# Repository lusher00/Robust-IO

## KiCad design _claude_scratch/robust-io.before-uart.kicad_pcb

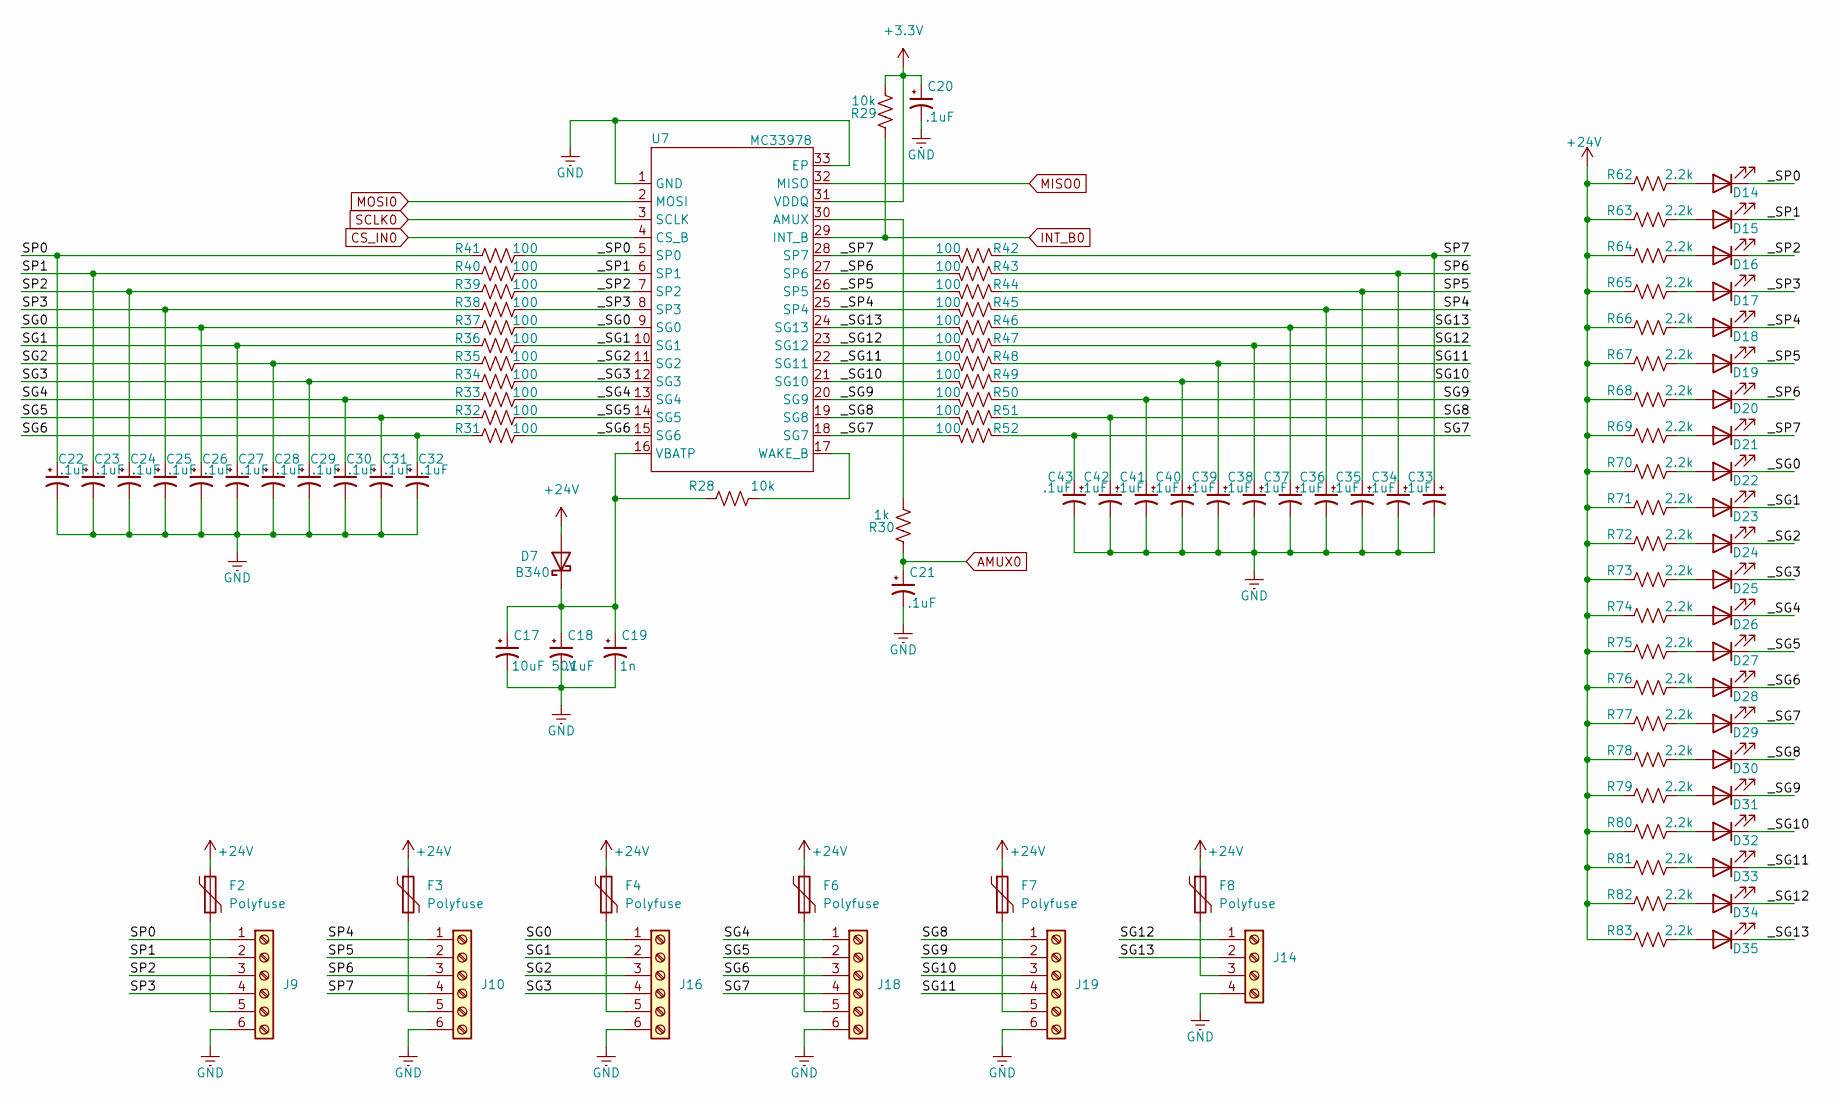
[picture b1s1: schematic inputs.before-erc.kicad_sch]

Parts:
C17: 10uF 50V; C_0805_2012Metric
C18, C20, C21, C22, C23, C24, C25, C26, C27, C28, C29, C30, C31, C32, C33, C34, C35, C36, C37, C38, C39, C40, C41, C42, C43: .1uF; C_0603_1608Metric
C19: 1n; C_0603_1608Metric
D7: B340; D_SMC
D14, D15, D16, D17, D18, D19, D20, D21, D22, D23, D24, D25, D26, D27, D28, D29, D30, D31, D32, D33, D34, D35: LED; LED_0603_1608Metric
F2, F3, F4, F6, F7, F8: Polyfuse; Fuse_1206_3216Metric
J9, J10, J16, J18, J19: Screw_Terminal_01x06; PhoenixContact_MC_1,5_6-G-3.5_1x06_P3.50mm_Horizontal
J14: Screw_Terminal_01x04; PhoenixContact_MC_1,5_4-G-3.5_1x04_P3.50mm_Horizontal
R28, R29: 10k; R_0603_1608Metric_Pad0.98x0.95mm_HandSolder
R30: 1k; R_0603_1608Metric_Pad0.98x0.95mm_HandSolder
R31, R32, R33, R34, R35, R36, R37, R38, R39, R40, R41, R42, R43, R44, R45, R46, R47, R48, R49, R50, R51, R52: 100; R_0603_1608Metric_Pad0.98x0.95mm_HandSolder
R62, R63, R64, R65, R66, R67, R68, R69, R70, R71, R72, R73, R74, R75, R76, R77, R78, R79, R80, R81, R82, R83: 2.2k; R_1206_3216Metric
U7: MC33978; HSOP-32-1EP_7.5x11mm_P0.65mm_EP4.7x4.7mm; Manufacturer Part MC33978AEKR2; LCSC Part Name MC33978AEKR2

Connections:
+3.3V: C20.1, R29.2, U7.31 (VDDQ); also elsewhere on the board
+24V: D7.2 (A), F2.1, F3.1, F4.1, F6.1, F7.1, F8.1, R62.1, R63.1, R64.1, R65.1, R66.1, R67.1, R68.1, R69.1, R70.1, R71.1, R72.1, R73.1, R74.1, R75.1, R76.1, R77.1, R78.1, R79.1, R80.1, R81.1, R82.1, R83.1; also elsewhere on the board
/inputs/SG0: C26.1, J16.1, R37.1
/inputs/SG1: C27.1, J16.2, R36.1
/inputs/SG2: C28.1, J16.3, R35.1
/inputs/SG3: C29.1, J16.4, R34.1
/inputs/SG4: C30.1, J18.1, R33.1
/inputs/SG5: C31.1, J18.2, R32.1
/inputs/SG6: C32.1, J18.3, R31.1
/inputs/SG7: C43.1, J18.4, R52.1
/inputs/SG8: C42.1, J19.1, R51.1
/inputs/SG9: C41.1, J19.2, R50.1
/inputs/SG10: C40.1, J19.3, R49.1
/inputs/SG11: C39.1, J19.4, R48.1
/inputs/SG12: C38.1, J14.1, R47.1
/inputs/SG13: C37.1, J14.2, R46.1
/inputs/SP0: C22.1, J9.1, R41.1
/inputs/SP1: C23.1, J9.2, R40.1
/inputs/SP2: C24.1, J9.3, R39.1
/inputs/SP3: C25.1, J9.4, R38.1
/inputs/SP4: C36.1, J10.1, R45.1
/inputs/SP5: C35.1, J10.2, R44.1
/inputs/SP6: C34.1, J10.3, R43.1
/inputs/SP7: C33.1, J10.4, R42.1
/inputs/_SG0: D22.1 (K), R37.2, U7.9 (SG0)
/inputs/_SG1: D23.1 (K), R36.2, U7.10 (SG1)
/inputs/_SG2: D24.1 (K), R35.2, U7.11 (SG2)
/inputs/_SG3: D25.1 (K), R34.2, U7.12 (SG3)
/inputs/_SG4: D26.1 (K), R33.2, U7.13 (SG4)
/inputs/_SG5: D27.1 (K), R32.2, U7.14 (SG5)
/inputs/_SG6: D28.1 (K), R31.2, U7.15 (SG6)
/inputs/_SG7: D29.1 (K), R52.2, U7.18 (SG7)
/inputs/_SG8: D30.1 (K), R51.2, U7.19 (SG8)
/inputs/_SG9: D31.1 (K), R50.2, U7.20 (SG9)
/inputs/_SG10: D32.1 (K), R49.2, U7.21 (SG10)
/inputs/_SG11: D33.1 (K), R48.2, U7.22 (SG11)
/inputs/_SG12: D34.1 (K), R47.2, U7.23 (SG12)
/inputs/_SG13: D35.1 (K), R46.2, U7.24 (SG13)
/inputs/_SP0: D14.1 (K), R41.2, U7.5 (SP0)
/inputs/_SP1: D15.1 (K), R40.2, U7.6 (SP1)
/inputs/_SP2: D16.1 (K), R39.2, U7.7 (SP2)
/inputs/_SP3: D17.1 (K), R38.2, U7.8 (SP3)
/inputs/_SP4: D18.1 (K), R45.2, U7.25 (SP4)
/inputs/_SP5: D19.1 (K), R44.2, U7.26 (SP5)
/inputs/_SP6: D20.1 (K), R43.2, U7.27 (SP6)
/inputs/_SP7: D21.1 (K), R42.2, U7.28 (SP7)
AMUX0: C21.1, R30.1; also elsewhere on the board
CS_IN0: U7.4 (CS_B); also elsewhere on the board
GND: C17.2, C18.2, C19.2, C20.2, C21.2, C22.2, C23.2, C24.2, C25.2, C26.2, C27.2, C28.2, C29.2, C30.2, C31.2, C32.2, C33.2, C34.2, C35.2, C36.2, C37.2, C38.2, C39.2, C40.2, C41.2, C42.2, C43.2, J9.6, J10.6, J14.4, J16.6, J18.6, J19.6, U7.1 (GND), U7.33 (EP); also elsewhere on the board
INT_B0: R29.1, U7.29 (INT_B); also elsewhere on the board
MISO0: U7.32 (MISO); also elsewhere on the board
MOSI0: U7.2 (MOSI); also elsewhere on the board
unnamed: C17.1, C18.1, C19.1, D7.1 (K), R28.1, U7.16 (VBATP)
unnamed: D14.2 (A), R62.2
unnamed: D15.2 (A), R63.2
unnamed: D16.2 (A), R64.2
unnamed: D17.2 (A), R65.2
unnamed: D18.2 (A), R66.2
unnamed: D19.2 (A), R67.2
unnamed: D20.2 (A), R68.2
unnamed: D21.2 (A), R69.2
unnamed: D22.2 (A), R70.2
unnamed: D23.2 (A), R71.2
unnamed: D24.2 (A), R72.2
unnamed: D25.2 (A), R73.2
unnamed: D26.2 (A), R74.2
unnamed: D27.2 (A), R75.2
unnamed: D28.2 (A), R76.2
unnamed: D29.2 (A), R77.2
unnamed: D30.2 (A), R78.2
unnamed: D31.2 (A), R79.2
unnamed: D32.2 (A), R80.2
unnamed: D33.2 (A), R81.2
unnamed: D34.2 (A), R82.2
unnamed: D35.2 (A), R83.2
unnamed: F2.2, J9.5
unnamed: F3.2, J10.5
unnamed: F8.2, J14.3
unnamed: F4.2, J16.5
unnamed: F6.2, J18.5
unnamed: F7.2, J19.5
unnamed: R30.2, U7.30 (AMUX)
unnamed: R28.2, U7.17 (WAKE_B)
SCLK0: U7.3 (SCLK); also elsewhere on the board

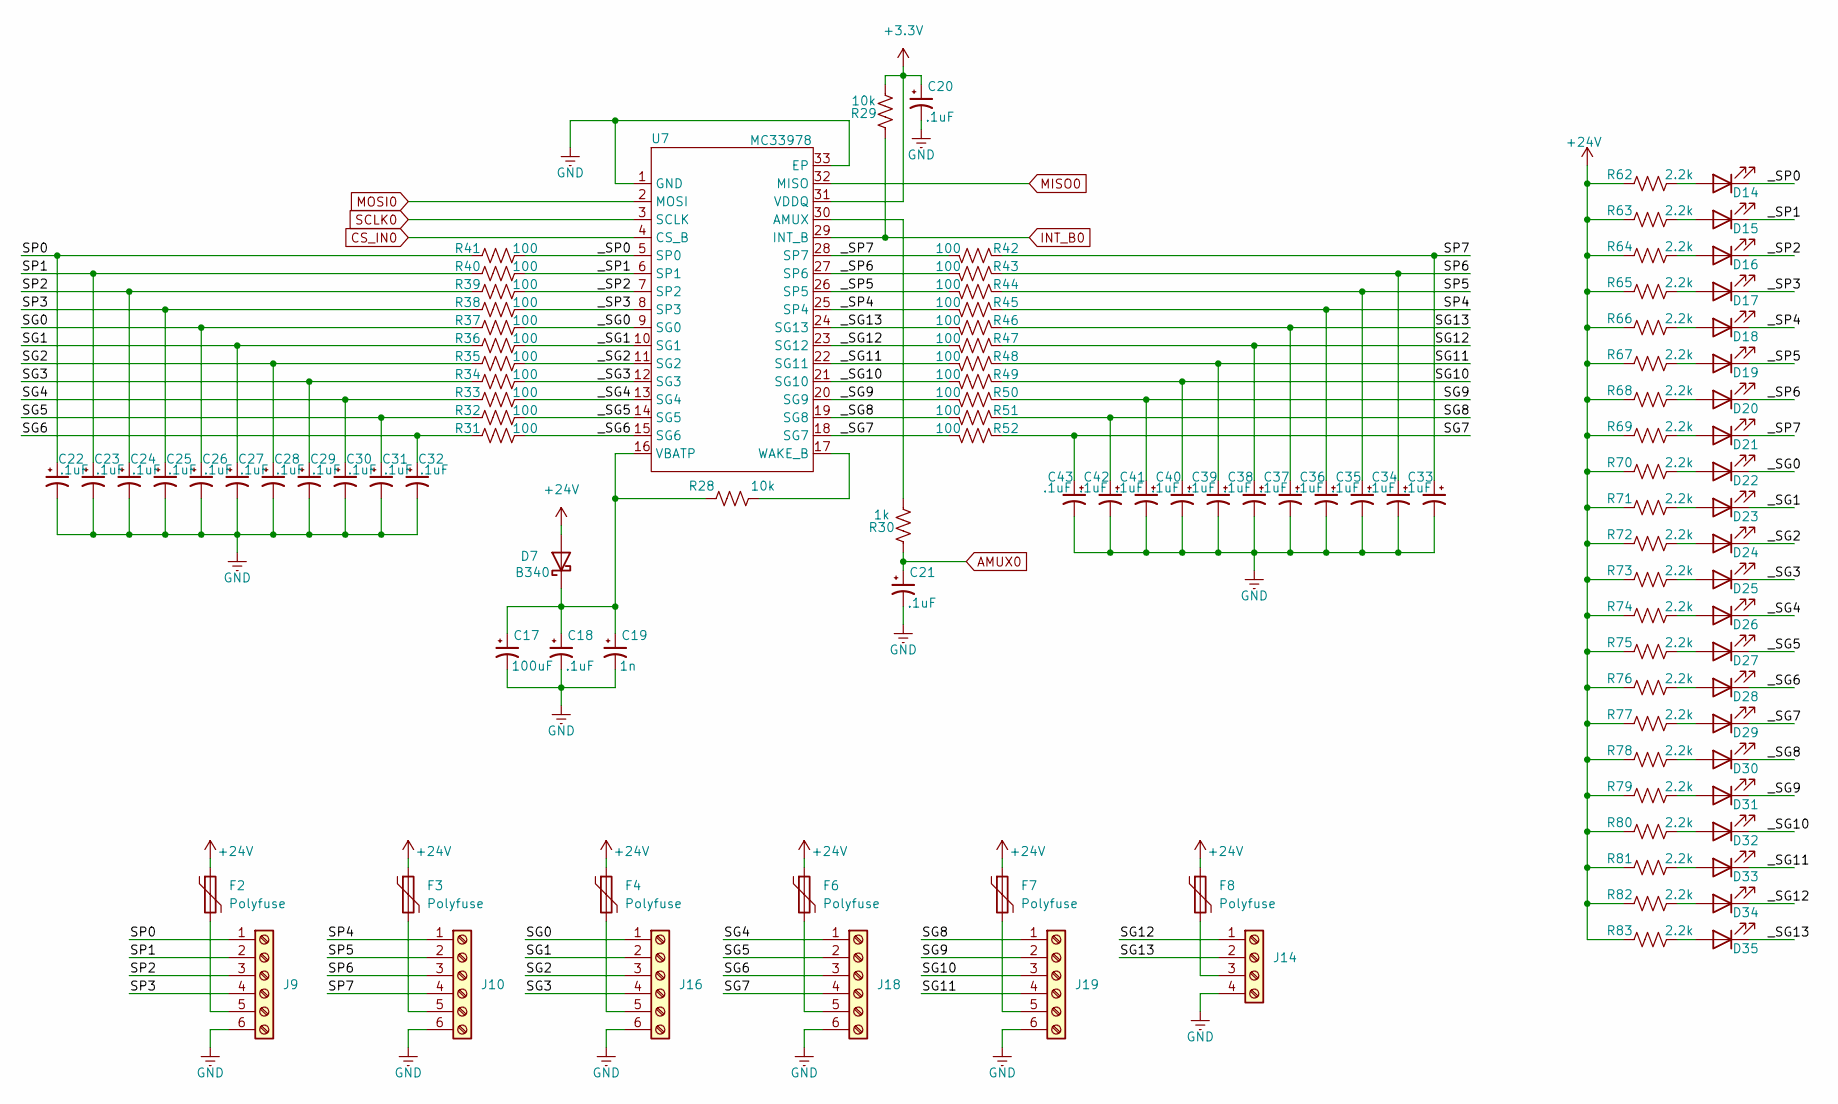
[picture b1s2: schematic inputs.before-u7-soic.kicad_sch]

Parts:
C17: 100uF; C_0603_1608Metric
C18, C20, C21, C22, C23, C24, C25, C26, C27, C28, C29, C30, C31, C32, C33, C34, C35, C36, C37, C38, C39, C40, C41, C42, C43: .1uF; C_0603_1608Metric
C19: 1n; C_0603_1608Metric
D7: B340; D_SMC
D14, D15, D16, D17, D18, D19, D20, D21, D22, D23, D24, D25, D26, D27, D28, D29, D30, D31, D32, D33, D34, D35: LED; LED_0603_1608Metric
F2, F3, F4, F6, F7, F8: Polyfuse; Fuse_1206_3216Metric
J9, J10, J16, J18, J19: Screw_Terminal_01x06; PhoenixContact_MC_1,5_6-G-3.5_1x06_P3.50mm_Horizontal
J14: Screw_Terminal_01x04; PhoenixContact_MC_1,5_4-G-3.5_1x04_P3.50mm_Horizontal
R28, R29: 10k; R_0603_1608Metric_Pad0.98x0.95mm_HandSolder
R30: 1k; R_0603_1608Metric_Pad0.98x0.95mm_HandSolder
R31, R32, R33, R34, R35, R36, R37, R38, R39, R40, R41, R42, R43, R44, R45, R46, R47, R48, R49, R50, R51, R52: 100; R_0603_1608Metric_Pad0.98x0.95mm_HandSolder
R62, R63, R64, R65, R66, R67, R68, R69, R70, R71, R72, R73, R74, R75, R76, R77, R78, R79, R80, R81, R82, R83: 2.2k; R_1206_3216Metric
U7: MC33978; QFN-32-1EP_5x5mm_P0.5mm_EP3.7x3.7mm_ThermalVias; Manufacturer Part MC33978AEKR2; LCSC Part Name MC33978AEKR2

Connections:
+3.3V: C20.1, R29.2, U7.31 (VDDQ); also elsewhere on the board
+24V: D7.2 (A), F2.1, F3.1, F4.1, F6.1, F7.1, F8.1, R62.1, R63.1, R64.1, R65.1, R66.1, R67.1, R68.1, R69.1, R70.1, R71.1, R72.1, R73.1, R74.1, R75.1, R76.1, R77.1, R78.1, R79.1, R80.1, R81.1, R82.1, R83.1; also elsewhere on the board
/inputs/SG0: C26.1, J16.1, R37.1
/inputs/SG1: C27.1, J16.2, R36.1
/inputs/SG2: C28.1, J16.3, R35.1
/inputs/SG3: C29.1, J16.4, R34.1
/inputs/SG4: C30.1, J18.1, R33.1
/inputs/SG5: C31.1, J18.2, R32.1
/inputs/SG6: C32.1, J18.3, R31.1
/inputs/SG7: C43.1, J18.4, R52.1
/inputs/SG8: C42.1, J19.1, R51.1
/inputs/SG9: C41.1, J19.2, R50.1
/inputs/SG10: C40.1, J19.3, R49.1
/inputs/SG11: C39.1, J19.4, R48.1
/inputs/SG12: C38.1, J14.1, R47.1
/inputs/SG13: C37.1, J14.2, R46.1
/inputs/SP0: C22.1, J9.1, R41.1
/inputs/SP1: C23.1, J9.2, R40.1
/inputs/SP2: C24.1, J9.3, R39.1
/inputs/SP3: C25.1, J9.4, R38.1
/inputs/SP4: C36.1, J10.1, R45.1
/inputs/SP5: C35.1, J10.2, R44.1
/inputs/SP6: C34.1, J10.3, R43.1
/inputs/SP7: C33.1, J10.4, R42.1
/inputs/_SG0: D22.1 (K), R37.2, U7.9 (SG0)
/inputs/_SG1: D23.1 (K), R36.2, U7.10 (SG1)
/inputs/_SG2: D24.1 (K), R35.2, U7.11 (SG2)
/inputs/_SG3: D25.1 (K), R34.2, U7.12 (SG3)
/inputs/_SG4: D26.1 (K), R33.2, U7.13 (SG4)
/inputs/_SG5: D27.1 (K), R32.2, U7.14 (SG5)
/inputs/_SG6: D28.1 (K), R31.2, U7.15 (SG6)
/inputs/_SG7: D29.1 (K), R52.2, U7.18 (SG7)
/inputs/_SG8: D30.1 (K), R51.2, U7.19 (SG8)
/inputs/_SG9: D31.1 (K), R50.2, U7.20 (SG9)
/inputs/_SG10: D32.1 (K), R49.2, U7.21 (SG10)
/inputs/_SG11: D33.1 (K), R48.2, U7.22 (SG11)
/inputs/_SG12: D34.1 (K), R47.2, U7.23 (SG12)
/inputs/_SG13: D35.1 (K), R46.2, U7.24 (SG13)
/inputs/_SP0: D14.1 (K), R41.2, U7.5 (SP0)
/inputs/_SP1: D15.1 (K), R40.2, U7.6 (SP1)
/inputs/_SP2: D16.1 (K), R39.2, U7.7 (SP2)
/inputs/_SP3: D17.1 (K), R38.2, U7.8 (SP3)
/inputs/_SP4: D18.1 (K), R45.2, U7.25 (SP4)
/inputs/_SP5: D19.1 (K), R44.2, U7.26 (SP5)
/inputs/_SP6: D20.1 (K), R43.2, U7.27 (SP6)
/inputs/_SP7: D21.1 (K), R42.2, U7.28 (SP7)
AMUX0: C21.1, R30.1; also elsewhere on the board
CS_IN0: U7.4 (CS_B); also elsewhere on the board
GND: C17.2, C18.2, C19.2, C20.2, C21.2, C22.2, C23.2, C24.2, C25.2, C26.2, C27.2, C28.2, C29.2, C30.2, C31.2, C32.2, C33.2, C34.2, C35.2, C36.2, C37.2, C38.2, C39.2, C40.2, C41.2, C42.2, C43.2, J9.6, J10.6, J14.4, J16.6, J18.6, J19.6, U7.1 (GND), U7.33 (EP); also elsewhere on the board
INT_B0: R29.1, U7.29 (INT_B); also elsewhere on the board
MISO0: U7.32 (MISO); also elsewhere on the board
MOSI0: U7.2 (MOSI); also elsewhere on the board
unnamed: C17.1, C18.1, C19.1, D7.1 (K), R28.1, U7.16 (VBATP)
unnamed: D14.2 (A), R62.2
unnamed: D15.2 (A), R63.2
unnamed: D16.2 (A), R64.2
unnamed: D17.2 (A), R65.2
unnamed: D18.2 (A), R66.2
unnamed: D19.2 (A), R67.2
unnamed: D20.2 (A), R68.2
unnamed: D21.2 (A), R69.2
unnamed: D22.2 (A), R70.2
unnamed: D23.2 (A), R71.2
unnamed: D24.2 (A), R72.2
unnamed: D25.2 (A), R73.2
unnamed: D26.2 (A), R74.2
unnamed: D27.2 (A), R75.2
unnamed: D28.2 (A), R76.2
unnamed: D29.2 (A), R77.2
unnamed: D30.2 (A), R78.2
unnamed: D31.2 (A), R79.2
unnamed: D32.2 (A), R80.2
unnamed: D33.2 (A), R81.2
unnamed: D34.2 (A), R82.2
unnamed: D35.2 (A), R83.2
unnamed: F2.2, J9.5
unnamed: F3.2, J10.5
unnamed: F8.2, J14.3
unnamed: F4.2, J16.5
unnamed: F6.2, J18.5
unnamed: F7.2, J19.5
unnamed: R30.2, U7.30 (AMUX)
unnamed: R28.2, U7.17 (WAKE_B)
SCLK0: U7.3 (SCLK); also elsewhere on the board

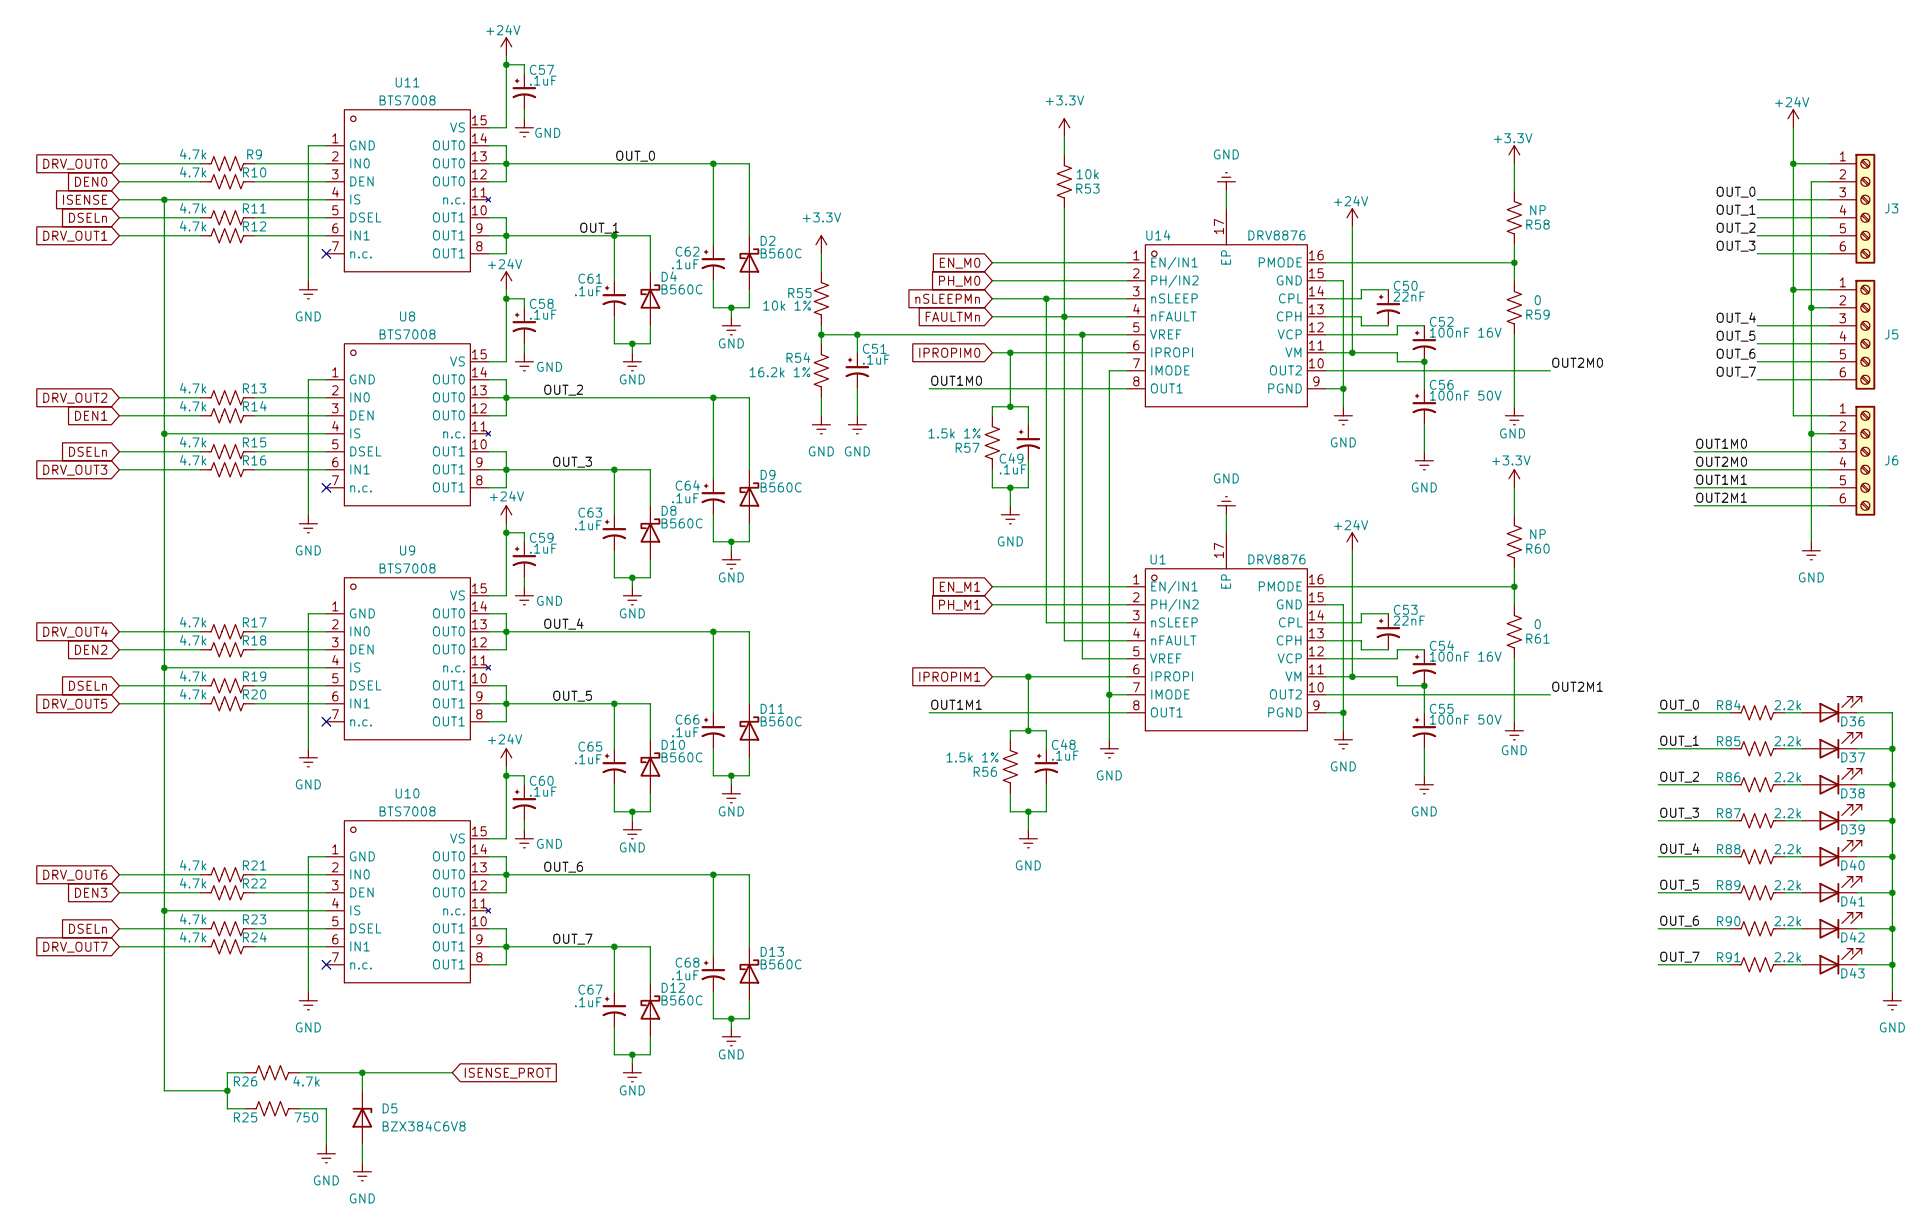
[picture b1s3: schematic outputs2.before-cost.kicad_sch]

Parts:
C48, C49, C51, C57, C58, C59, C60, C61, C62, C63, C64, C65, C66, C67, C68: .1uF; C_0603_1608Metric_Pad1.08x0.95mm_HandSolder
C50, C53: 22nF; C_0603_1608Metric_Pad1.08x0.95mm_HandSolder
C52, C54: 100nF 16V; C_0603_1608Metric_Pad1.08x0.95mm_HandSolder
C55, C56: 100nF 50V; C_0603_1608Metric_Pad1.08x0.95mm_HandSolder
D2, D4, D8, D9, D10, D11, D12, D13: B560C; D_SMC
D5: BZX384C6V8; D_SOD-323
D36, D37, D38, D39, D40, D41, D42, D43: LED; LED_0603_1608Metric
J3, J5, J6: Screw_Terminal_01x06; PhoenixContact_MSTBA_2,5_6-G-5,08_1x06_P5.08mm_Horizontal
R9, R10, R11, R12, R13, R14, R15, R16, R17, R18, R19, R20, R21, R22, R23, R24, R26: 4.7k; R_0603_1608Metric
R25: 750; R_0603_1608Metric
R53: 10k; R_0603_1608Metric_Pad0.98x0.95mm_HandSolder
R54: 16.2k 1%; R_0603_1608Metric_Pad0.98x0.95mm_HandSolder
R55: 10k 1%; R_0603_1608Metric_Pad0.98x0.95mm_HandSolder
R56, R57: 1.5k 1%; R_0603_1608Metric_Pad0.98x0.95mm_HandSolder
R58, R60: NP; R_0603_1608Metric_Pad0.98x0.95mm_HandSolder
R59, R61: 0; R_0603_1608Metric_Pad0.98x0.95mm_HandSolder
R84, R85, R86, R87, R88, R89, R90, R91: 2.2k; R_0603_1608Metric_Pad0.98x0.95mm_HandSolder
U1, U14: DRV8876; IC_DRV8876PWPR; Manufacturer Part DRV8876PWPR; LCSC Part Name 3.5A 有刷直流电机驱动芯片 5.5V
U8, U9, U10, U11: BTS7008; TSSOP-14-1EP_4.4x5mm_P0.65mm; Manufacturer Part BTS7008-2EPA; LCSC Part Name 12V智能高端功率开关

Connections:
+3.3V: R53.1, R55.1, R58.1, R60.1; also elsewhere on the board
+24V: C52.2, C54.2, C55.1, C56.1, C57.1, C58.1, C59.1, C60.1, J3.1, J5.1, J6.1, U1.11 (VM), U8.15 (VS), U9.15 (VS), U10.15 (VS), U11.15 (VS), U14.11 (VM); also elsewhere on the board
/outputs2/OUT1M0: J6.3, U14.8 (OUT1)
/outputs2/OUT1M1: J6.5, U1.8 (OUT1)
/outputs2/OUT2M0: J6.4, U14.10 (OUT2)
/outputs2/OUT2M1: J6.6, U1.10 (OUT2)
/outputs2/OUT_0: C62.1, D2.1 (K), J3.3, R84.1, U11.12 (OUT0), U11.13 (OUT0), U11.14 (OUT0)
/outputs2/OUT_1: C61.1, D4.1 (K), J3.4, R85.1, U11.8 (OUT1), U11.9 (OUT1), U11.10 (OUT1)
/outputs2/OUT_2: C64.1, D9.1 (K), J3.5, R86.1, U8.12 (OUT0), U8.13 (OUT0), U8.14 (OUT0)
/outputs2/OUT_3: C63.1, D8.1 (K), J3.6, R87.1, U8.8 (OUT1), U8.9 (OUT1), U8.10 (OUT1)
/outputs2/OUT_4: C66.1, D11.1 (K), J5.3, R88.1, U9.12 (OUT0), U9.13 (OUT0), U9.14 (OUT0)
/outputs2/OUT_5: C65.1, D10.1 (K), J5.4, R89.1, U9.8 (OUT1), U9.9 (OUT1), U9.10 (OUT1)
/outputs2/OUT_6: C68.1, D13.1 (K), J5.5, R90.1, U10.12 (OUT0), U10.13 (OUT0), U10.14 (OUT0)
/outputs2/OUT_7: C67.1, D12.1 (K), J5.6, R91.1, U10.8 (OUT1), U10.9 (OUT1), U10.10 (OUT1)
DEN0: R10.1; also elsewhere on the board
DEN1: R14.1; also elsewhere on the board
DEN2: R18.1; also elsewhere on the board
DEN3: R22.1; also elsewhere on the board
DRV_OUT0: R9.1; also elsewhere on the board
DRV_OUT1: R12.1; also elsewhere on the board
DRV_OUT2: R13.1; also elsewhere on the board
DRV_OUT3: R16.1; also elsewhere on the board
DRV_OUT4: R17.1; also elsewhere on the board
DRV_OUT5: R20.1; also elsewhere on the board
DRV_OUT6: R21.1; also elsewhere on the board
DRV_OUT7: R24.1; also elsewhere on the board
DSELn: R11.1, R15.1, R19.1, R23.1; also elsewhere on the board
EN_M0: U14.1 (EN/IN1); also elsewhere on the board
EN_M1: U1.1 (EN/IN1); also elsewhere on the board
FAULTMn: R53.2, U1.4 (nFAULT), U14.4 (nFAULT); also elsewhere on the board
GND: C48.2, C49.2, C51.2, C55.2, C56.2, C57.2, C58.2, C59.2, C60.2, C61.2, C62.2, C63.2, C64.2, C65.2, C66.2, C67.2, C68.2, D2.2 (A), D4.2 (A), D5.2 (A), D8.2 (A), D9.2 (A), D10.2 (A), D11.2 (A), D12.2 (A), D13.2 (A), D36.1 (K), D37.1 (K), D38.1 (K), D39.1 (K), D40.1 (K), D41.1 (K), D42.1 (K), D43.1 (K), J3.2, J5.2, J6.2, R25.1, R54.2, R56.2, R57.2, R59.2, R61.2, U1.7 (IMODE), U1.9 (PGND), U1.15 (GND), U1.17 (EP), U8.1 (GND), U9.1 (GND), U10.1 (GND), U11.1 (GND), U14.7 (IMODE), U14.9 (PGND), U14.15 (GND), U14.17 (EP); also elsewhere on the board
IPROPIM0: C49.1, R57.1, U14.6 (IPROPI); also elsewhere on the board
IPROPIM1: C48.1, R56.1, U1.6 (IPROPI); also elsewhere on the board
ISENSE: R25.2, R26.2, U8.4 (IS), U9.4 (IS), U10.4 (IS), U11.4 (IS)
ISENSE_PROT: D5.1 (K), R26.1; also elsewhere on the board
unnamed: D36.2 (A), R84.2
unnamed: D37.2 (A), R85.2
unnamed: D38.2 (A), R86.2
unnamed: D39.2 (A), R87.2
unnamed: D40.2 (A), R88.2
unnamed: D41.2 (A), R89.2
unnamed: D42.2 (A), R90.2
unnamed: D43.2 (A), R91.2
unnamed: C53.2, U1.13 (CPH)
unnamed: C53.1, U1.14 (CPL)
unnamed: R60.2, R61.1, U1.16 (PMODE)
unnamed: C54.1, U1.12 (VCP)
unnamed: C51.1, R54.1, R55.2, U1.5 (VREF), U14.5 (VREF)
unnamed: R14.2, U8.3 (DEN)
unnamed: R15.2, U8.5 (DSEL)
unnamed: R13.2, U8.2 (IN0)
unnamed: R16.2, U8.6 (IN1)
unnamed: R18.2, U9.3 (DEN)
unnamed: R19.2, U9.5 (DSEL)
unnamed: R17.2, U9.2 (IN0)
unnamed: R20.2, U9.6 (IN1)
unnamed: R22.2, U10.3 (DEN)
unnamed: R23.2, U10.5 (DSEL)
unnamed: R21.2, U10.2 (IN0)
unnamed: R24.2, U10.6 (IN1)
unnamed: R10.2, U11.3 (DEN)
unnamed: R11.2, U11.5 (DSEL)
unnamed: R9.2, U11.2 (IN0)
unnamed: R12.2, U11.6 (IN1)
unnamed: C50.2, U14.13 (CPH)
unnamed: C50.1, U14.14 (CPL)
unnamed: R58.2, R59.1, U14.16 (PMODE)
unnamed: C52.1, U14.12 (VCP)
PH_M0: U14.2 (PH/IN2); also elsewhere on the board
PH_M1: U1.2 (PH/IN2); also elsewhere on the board
nSLEEPMn: U1.3 (nSLEEP), U14.3 (nSLEEP); also elsewhere on the board

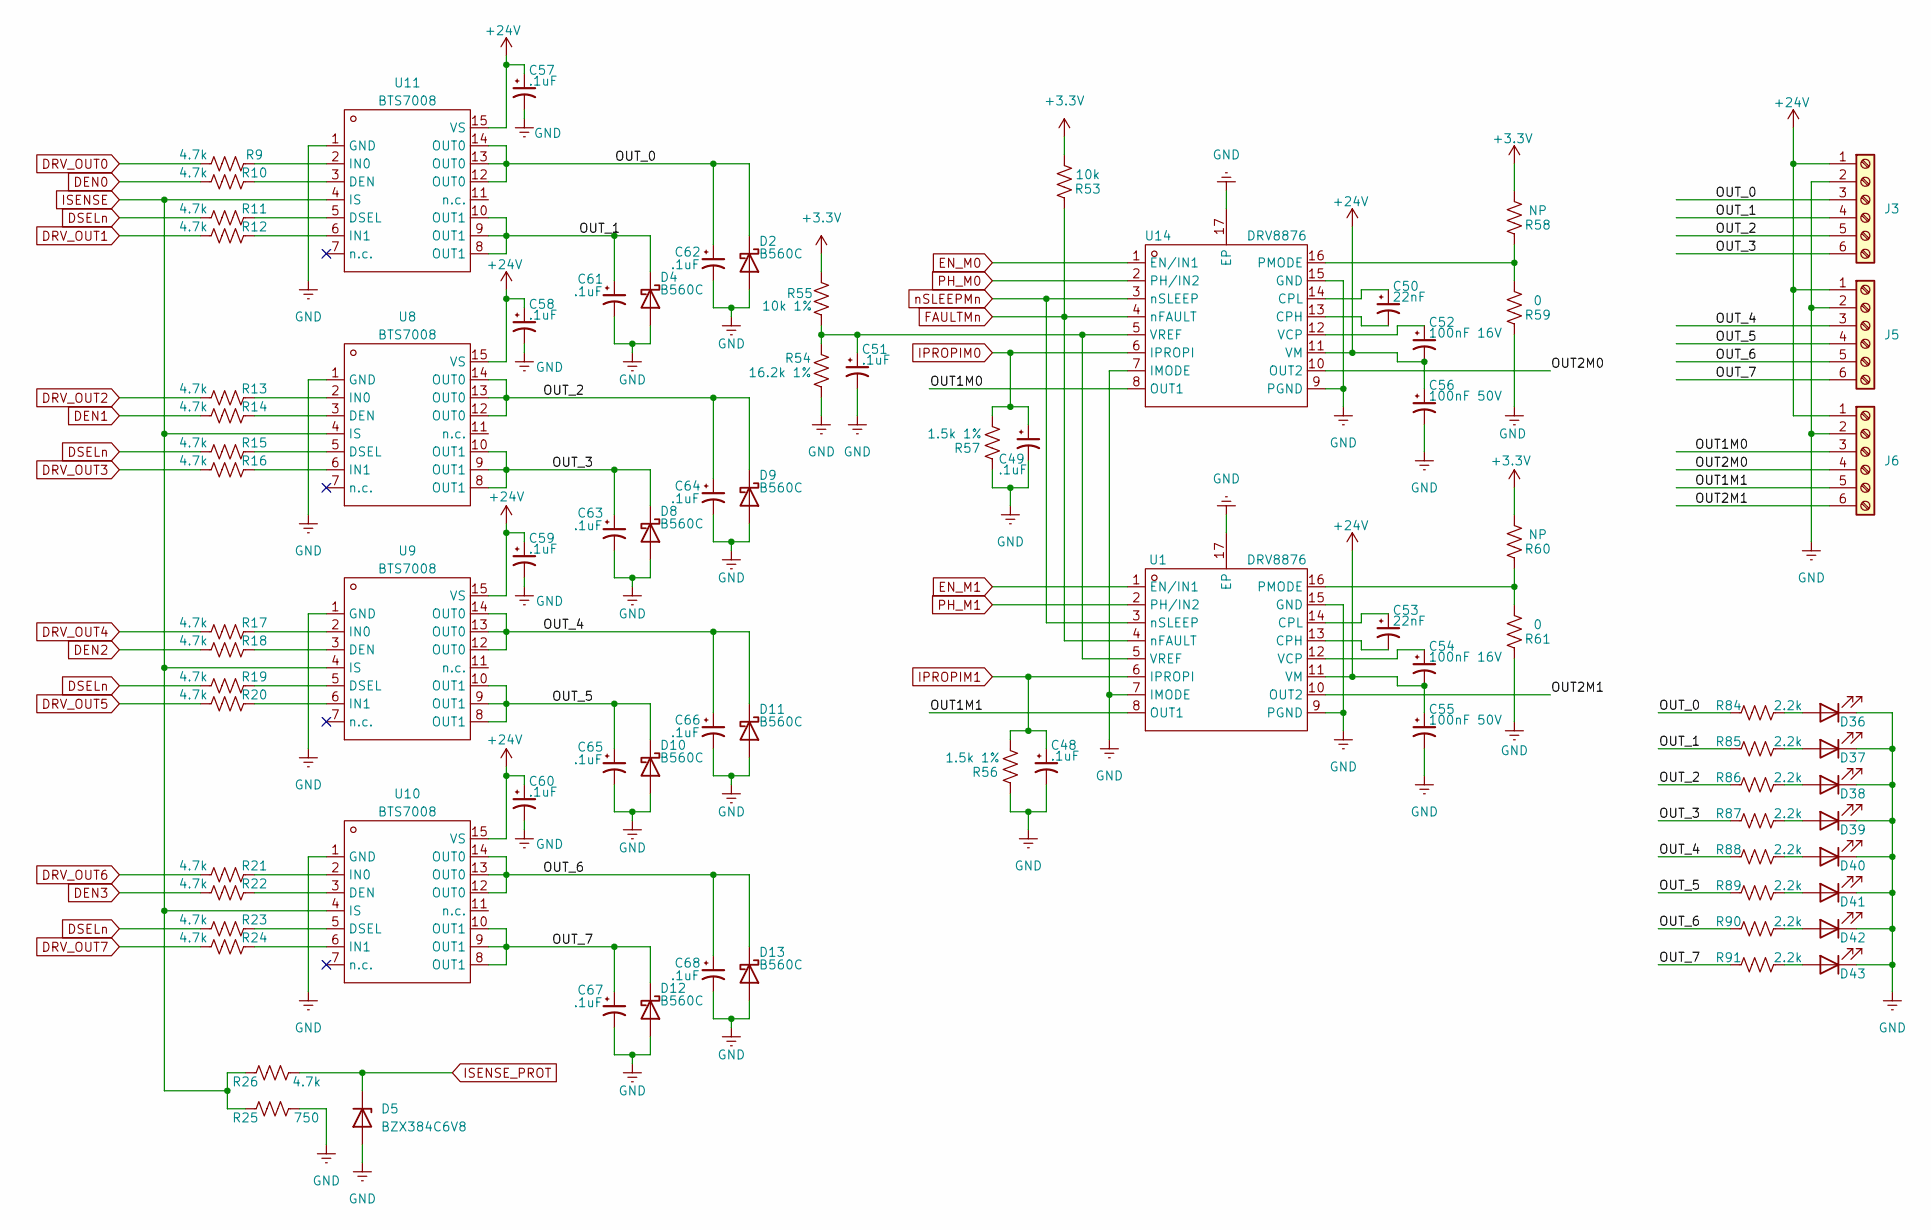
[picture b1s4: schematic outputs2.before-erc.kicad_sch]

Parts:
C48, C49, C51, C57, C58, C59, C60, C61, C62, C63, C64, C65, C66, C67, C68: .1uF; C_0603_1608Metric_Pad1.08x0.95mm_HandSolder
C50, C53: 22nF; C_0603_1608Metric_Pad1.08x0.95mm_HandSolder
C52, C54: 100nF 16V; C_0603_1608Metric_Pad1.08x0.95mm_HandSolder
C55, C56: 100nF 50V; C_0603_1608Metric_Pad1.08x0.95mm_HandSolder
D2, D4, D8, D9, D10, D11, D12, D13: B560C; D_SMC
D5: BZX384C6V8; D_SOD-323
D36, D37, D38, D39, D40, D41, D42, D43: LED; LED_0603_1608Metric
J3, J5, J6: Screw_Terminal_01x06; PhoenixContact_MSTBA_2,5_6-G-5,08_1x06_P5.08mm_Horizontal
R9, R10, R11, R12, R13, R14, R15, R16, R17, R18, R19, R20, R21, R22, R23, R24, R26: 4.7k; R_0603_1608Metric
R25: 750; R_0603_1608Metric
R53: 10k; R_0603_1608Metric_Pad0.98x0.95mm_HandSolder
R54: 16.2k 1%; R_0603_1608Metric_Pad0.98x0.95mm_HandSolder
R55: 10k 1%; R_0603_1608Metric_Pad0.98x0.95mm_HandSolder
R56, R57: 1.5k 1%; R_0603_1608Metric_Pad0.98x0.95mm_HandSolder
R58, R60: NP; R_0603_1608Metric_Pad0.98x0.95mm_HandSolder
R59, R61: 0; R_0603_1608Metric_Pad0.98x0.95mm_HandSolder
R84, R85, R86, R87, R88, R89, R90, R91: 2.2k; R_0603_1608Metric_Pad0.98x0.95mm_HandSolder
U1, U14: DRV8876; IC_DRV8876PWPR; Manufacturer Part DRV8876PWPR; LCSC Part Name 3.5A 有刷直流电机驱动芯片 5.5V
U8, U9, U10, U11: BTS7008; TSSOP-14-1EP_4.4x5mm_P0.65mm; Manufacturer Part BTS7008-2EPA; LCSC Part Name 12V智能高端功率开关

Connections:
+3.3V: R53.1, R55.1, R58.1, R60.1; also elsewhere on the board
+24V: C52.2, C54.2, C55.1, C56.1, C57.1, C58.1, C59.1, C60.1, J3.1, J5.1, J6.1, U1.11 (VM), U8.15 (VS), U9.15 (VS), U10.15 (VS), U11.15 (VS), U14.11 (VM); also elsewhere on the board
/outputs2/OUT1M0: J6.3, U14.8 (OUT1)
/outputs2/OUT1M1: J6.5, U1.8 (OUT1)
/outputs2/OUT2M0: J6.4, U14.10 (OUT2)
/outputs2/OUT2M1: J6.6, U1.10 (OUT2)
/outputs2/OUT_0: C62.1, D2.1 (K), J3.3, R84.1, U11.12 (OUT0), U11.13 (OUT0), U11.14 (OUT0)
/outputs2/OUT_1: C61.1, D4.1 (K), J3.4, R85.1, U11.8 (OUT1), U11.9 (OUT1), U11.10 (OUT1)
/outputs2/OUT_2: C64.1, D9.1 (K), J3.5, R86.1, U8.12 (OUT0), U8.13 (OUT0), U8.14 (OUT0)
/outputs2/OUT_3: C63.1, D8.1 (K), J3.6, R87.1, U8.8 (OUT1), U8.9 (OUT1), U8.10 (OUT1)
/outputs2/OUT_4: C66.1, D11.1 (K), J5.3, R88.1, U9.12 (OUT0), U9.13 (OUT0), U9.14 (OUT0)
/outputs2/OUT_5: C65.1, D10.1 (K), J5.4, R89.1, U9.8 (OUT1), U9.9 (OUT1), U9.10 (OUT1)
/outputs2/OUT_6: C68.1, D13.1 (K), J5.5, R90.1, U10.12 (OUT0), U10.13 (OUT0), U10.14 (OUT0)
/outputs2/OUT_7: C67.1, D12.1 (K), J5.6, R91.1, U10.8 (OUT1), U10.9 (OUT1), U10.10 (OUT1)
DEN0: R10.1; also elsewhere on the board
DEN1: R14.1; also elsewhere on the board
DEN2: R18.1; also elsewhere on the board
DEN3: R22.1; also elsewhere on the board
DRV_OUT0: R9.1; also elsewhere on the board
DRV_OUT1: R12.1; also elsewhere on the board
DRV_OUT2: R13.1; also elsewhere on the board
DRV_OUT3: R16.1; also elsewhere on the board
DRV_OUT4: R17.1; also elsewhere on the board
DRV_OUT5: R20.1; also elsewhere on the board
DRV_OUT6: R21.1; also elsewhere on the board
DRV_OUT7: R24.1; also elsewhere on the board
DSELn: R11.1, R15.1, R19.1, R23.1; also elsewhere on the board
EN_M0: U14.1 (EN/IN1); also elsewhere on the board
EN_M1: U1.1 (EN/IN1); also elsewhere on the board
FAULTMn: R53.2, U1.4 (nFAULT), U14.4 (nFAULT); also elsewhere on the board
GND: C48.2, C49.2, C51.2, C55.2, C56.2, C57.2, C58.2, C59.2, C60.2, C61.2, C62.2, C63.2, C64.2, C65.2, C66.2, C67.2, C68.2, D2.2 (A), D4.2 (A), D5.2 (A), D8.2 (A), D9.2 (A), D10.2 (A), D11.2 (A), D12.2 (A), D13.2 (A), D36.1 (K), D37.1 (K), D38.1 (K), D39.1 (K), D40.1 (K), D41.1 (K), D42.1 (K), D43.1 (K), J3.2, J5.2, J6.2, R25.1, R54.2, R56.2, R57.2, R59.2, R61.2, U1.7 (IMODE), U1.9 (PGND), U1.15 (GND), U1.17 (EP), U8.1 (GND), U9.1 (GND), U10.1 (GND), U11.1 (GND), U14.7 (IMODE), U14.9 (PGND), U14.15 (GND), U14.17 (EP); also elsewhere on the board
IPROPIM0: C49.1, R57.1, U14.6 (IPROPI); also elsewhere on the board
IPROPIM1: C48.1, R56.1, U1.6 (IPROPI); also elsewhere on the board
ISENSE: R25.2, R26.2, U8.4 (IS), U9.4 (IS), U10.4 (IS), U11.4 (IS)
ISENSE_PROT: D5.1 (K), R26.1; also elsewhere on the board
unnamed: D36.2 (A), R84.2
unnamed: D37.2 (A), R85.2
unnamed: D38.2 (A), R86.2
unnamed: D39.2 (A), R87.2
unnamed: D40.2 (A), R88.2
unnamed: D41.2 (A), R89.2
unnamed: D42.2 (A), R90.2
unnamed: D43.2 (A), R91.2
unnamed: C53.2, U1.13 (CPH)
unnamed: C53.1, U1.14 (CPL)
unnamed: R60.2, R61.1, U1.16 (PMODE)
unnamed: C54.1, U1.12 (VCP)
unnamed: C51.1, R54.1, R55.2, U1.5 (VREF), U14.5 (VREF)
unnamed: R14.2, U8.3 (DEN)
unnamed: R15.2, U8.5 (DSEL)
unnamed: R13.2, U8.2 (IN0)
unnamed: R16.2, U8.6 (IN1)
unnamed: R18.2, U9.3 (DEN)
unnamed: R19.2, U9.5 (DSEL)
unnamed: R17.2, U9.2 (IN0)
unnamed: R20.2, U9.6 (IN1)
unnamed: R22.2, U10.3 (DEN)
unnamed: R23.2, U10.5 (DSEL)
unnamed: R21.2, U10.2 (IN0)
unnamed: R24.2, U10.6 (IN1)
unnamed: R10.2, U11.3 (DEN)
unnamed: R11.2, U11.5 (DSEL)
unnamed: R9.2, U11.2 (IN0)
unnamed: R12.2, U11.6 (IN1)
unnamed: C50.2, U14.13 (CPH)
unnamed: C50.1, U14.14 (CPL)
unnamed: R58.2, R59.1, U14.16 (PMODE)
unnamed: C52.1, U14.12 (VCP)
PH_M0: U14.2 (PH/IN2); also elsewhere on the board
PH_M1: U1.2 (PH/IN2); also elsewhere on the board
nSLEEPMn: U1.3 (nSLEEP), U14.3 (nSLEEP); also elsewhere on the board

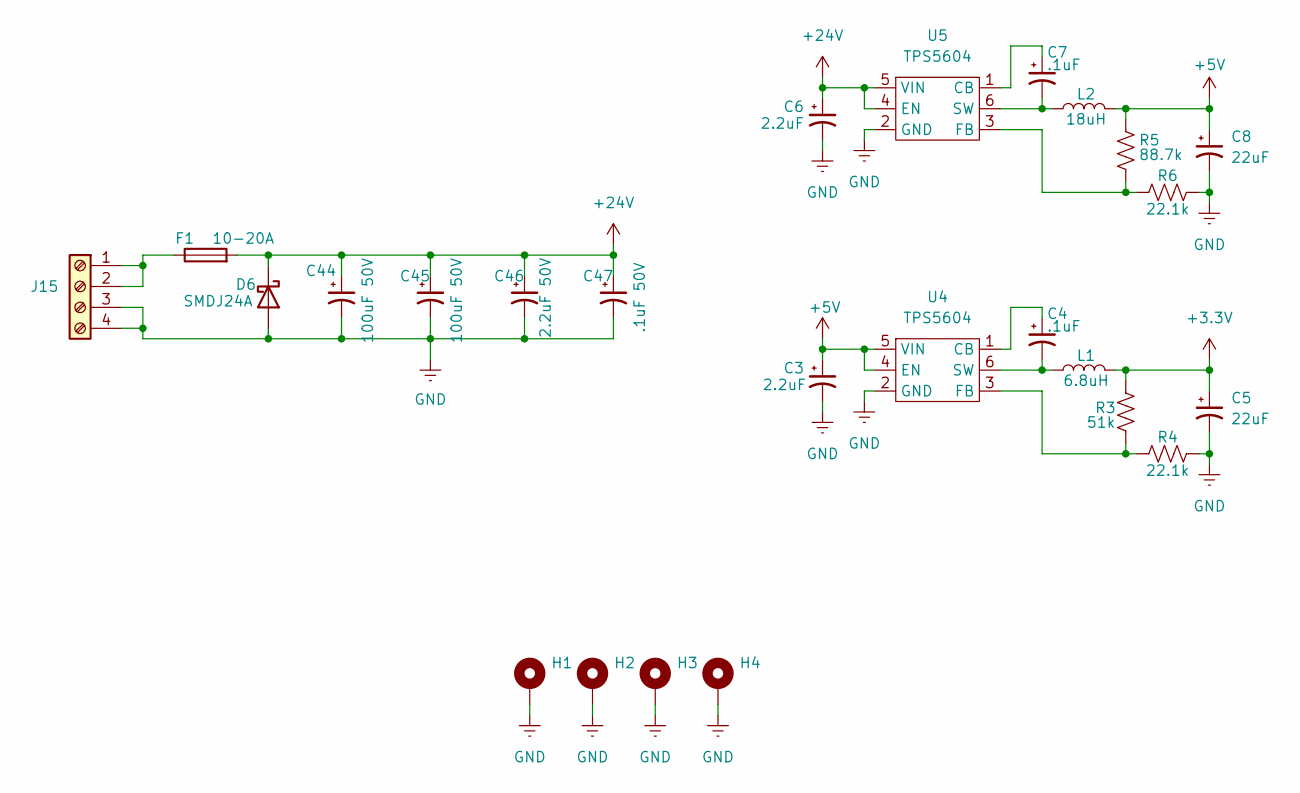
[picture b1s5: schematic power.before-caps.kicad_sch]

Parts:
C3, C6: 2.2uF; C_0805_2012Metric_Pad1.18x1.45mm_HandSolder
C4, C7: .1uF; C_0603_1608Metric_Pad1.08x0.95mm_HandSolder
C5, C8: 22uF; C_0603_1608Metric_Pad1.08x0.95mm_HandSolder
C44, C45: 100uF 50V; C_0805_2012Metric_Pad1.18x1.45mm_HandSolder
C46: 2.2uF 50V; C_0805_2012Metric_Pad1.18x1.45mm_HandSolder
C47: .1uF 50V; C_0805_2012Metric_Pad1.18x1.45mm_HandSolder
D6: SMDJ24A; D_SMC
F1: 10-20A; Fuseholder_Blade_Mini_Keystone_3568
H1, H2, H3, H4: MountingHole_Pad; MountingHole_3.2mm_M3_DIN965_Pad_TopBottom
J15: Screw_Terminal_01x04; PhoenixContact_MSTBA_2,5_4-G-5,08_1x04_P5.08mm_Horizontal
L1: 6.8uH; L_0805_2012Metric_Pad1.05x1.20mm_HandSolder; Part Number CB2016T6R8M
L2: 18uH; L_0805_2012Metric
R3: 51k; R_0603_1608Metric_Pad0.98x0.95mm_HandSolder
R4, R6: 22.1k; R_0603_1608Metric_Pad0.98x0.95mm_HandSolder
R5: 88.7k; R_0603_1608Metric_Pad0.98x0.95mm_HandSolder
U4, U5: TPS5604; SOT-23-6

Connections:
+3.3V: C5.1, L1.2, R3.1; also elsewhere on the board
+5V: C3.1, C8.1, L2.2, R5.1, U4.4 (EN), U4.5 (VIN); also elsewhere on the board
+24V: C6.1, C44.1, C45.1, C46.1, C47.1, D6.1 (K), F1.2, U5.4 (EN), U5.5 (VIN); also elsewhere on the board
GND: C3.2, C5.2, C6.2, C8.2, C44.2, C45.2, C46.2, C47.2, D6.2 (A), H1.1 (1_1), H2.1 (1_1), H3.1 (1_1), H4.1 (1_1), J15.3, J15.4, R4.1, R6.1, U4.2 (GND), U5.2 (GND); also elsewhere on the board
unnamed: F1.1, J15.1, J15.2
unnamed: C4.1, U4.1 (CB)
unnamed: R3.2, R4.2, U4.3 (FB)
unnamed: C4.2, L1.1, U4.6 (SW)
unnamed: C7.1, U5.1 (CB)
unnamed: R5.2, R6.2, U5.3 (FB)
unnamed: C7.2, L2.1, U5.6 (SW)
